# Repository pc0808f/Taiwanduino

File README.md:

# Taiwanduino

Hi, this is the official project site of Taiwanduino
* For our hardware design, please go to [/hardware][hw]
* Our software stuff (bootloader, driver, Arduino sketch...etc) is at [/software][sw]
* Our holder model has been released, it's located at [/holder][hd]

For installation or assembly instructions, see our [Wiki page][wiki]
Like our facebook [fan page][fb] for more info, online shop or donations!

[Changelog]
2025/11/05 (pc0808f fork) - v1.0.3
Fixed: Support for USBasp/USBtiny programmer with custom USB ID 1209:5457
Changed: Reverted to v1.0.2 style using arduino:usbtiny as upload tool
Programmer: "Taiwanduino" option available (uses local avrdude.conf for custom USB IDs)
Note: Direct upload uses Arduino core tools; "Upload Using Programmer" supports VID:1209 PID:5457

2025/10/29 (pc0808f fork) - v1.0.2
Fixed: Examples now visible in Arduino IDE after Board Manager installation
Added library.properties file for bundled library
Updated board package structure to follow Arduino specification

2025/10/28 (pc0808f fork) - v1.0.1
Updated board manager URL to pc0808f fork version
Re-committed zip file for GitHub Pages sync

2017/9/24
Add a 7 tones simple instrument example sketch

2016/11/11
Support for the latest CapacitiveSensor library from the Library Manager

2016/10/31
Holder v1.0 released

2016/10/27
Add pcm audio converter tools/pcm_converter
Cleanup example sketches

***

*Read this in other languages: [English](README.md), [繁體中文](README.zh-TW.md).*

   [wiki]: <https://github.com/pc0808f/Taiwanduino/wiki>
   [hw]: <https://github.com/pc0808f/Taiwanduino/tree/master/hardware>
   [sw]: <https://github.com/pc0808f/Taiwanduino/tree/master/software>
   [hd]: <https://github.com/pc0808f/Taiwanduino/tree/master/holder>
   [fb]: <https://www.facebook.com/Taiwanduino>

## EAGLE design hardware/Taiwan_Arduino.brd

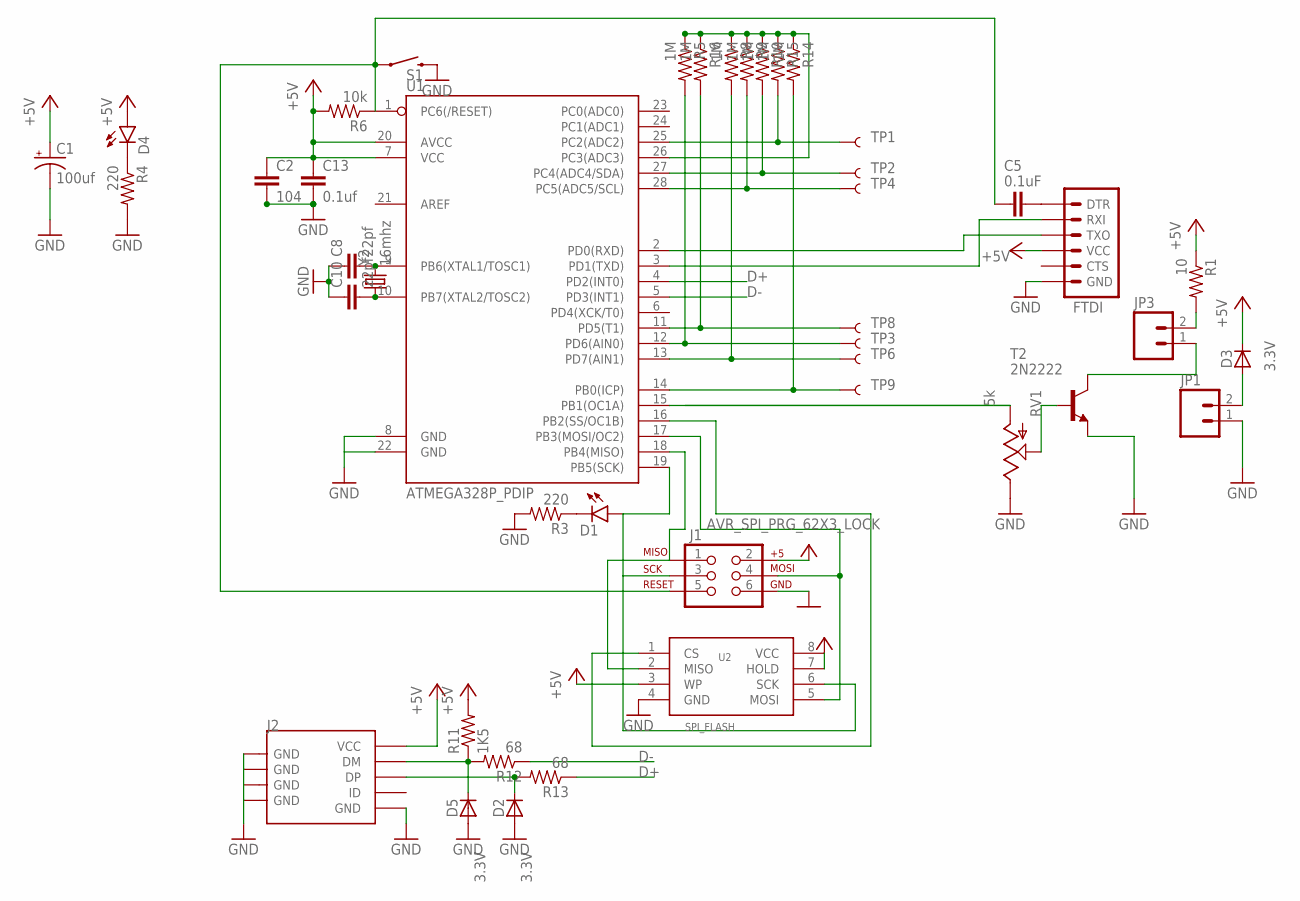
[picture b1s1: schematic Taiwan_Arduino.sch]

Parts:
C1: 100uf; E2,5-5
C2: 104; CAP-PTH-5MM
C5: 0.1uF; CAP-PTH-5MM
C8, C10: 22pf; CAP-PTH-5MM
C13: 0.1uf; CAP-PTH-5MM
D1, D4: LED3MM
D2, D3, D5: 3.3V; 0204V
FTDI: ARDUINO_SERIAL_PROGRAMLOCK; 1X06_LOCK
J1: AVR_SPI_PRG_62X3_LOCK; 2X3_LOCK
J2: USB-MINIUSB-5P-TH; MINI-5P
JP1: Battery; 1X02
JP3: M021X02_NO_SILK; 1X02_NO_SILK
R1: 10; AXIAL-0.1
R3, R4: 220; AXIAL-0.1
R5, R8, R9, R10, R15, R16: 1M; AXIAL-0.1
R6: 10k; AXIAL-0.1
R11: 1K5; AXIAL-0.1
R12, R13: 68; AXIAL-0.1
R14: 1M; AXIAL-0.4
RV1: 5k; ALPS_POT
S1: SWITCH-MOMENTARY-2PTH; TACTILE-PTH
T2: 2N2222; TO92-EBC-OVAL
TP1, TP2, TP3, TP4, TP6, TP8, TP9: TEST-POINT; PADBIG
U1: ATMEGA328P_PDIP; DIL28-3
U2: SPI_FLASH; DIL08
Y2: 16mhz; HC49U-V

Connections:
1: R8.P$2 (2), TP6.P$1, U1.13 (PD7(AIN1))
+5V: C1.+, C2.1, C13.1, D3.2 (C), D4.A, FTDI.4 (VCC), J1.2, J2.VCC, R1.P$1 (1), R6.P$2 (2), R11.P$2 (2), U1.7 (VCC), U1.20 (AVCC), U2.3 (WP), U2.7 (HOLD), U2.8 (VCC)
D+: R13.P$1 (1), U1.4 (PD2(INT0))
D-: R12.P$1 (1), U1.5 (PD3(INT1))
GND: C1.-, C2.2, C8.1, C10.1, C13.2, D2.1 (A), D5.1 (A), FTDI.6 (GND), J1.6, J2.GND, J2.S1 (GND), J2.S2 (GND), J2.S3 (GND), J2.S4 (GND), JP1.1, R3.P$2 (2), R4.P$2 (2), RV1.P$1 (E), S1.3 (2), T2.E, U1.8 (GND), U1.22 (GND), U2.4 (GND)
unnamed: JP3.2, R1.P$2 (2)
unnamed: RV1.P$3 (A), U1.15 (PB1(OC1A))
unnamed: R14.P$2 (2), TP9.P$1, U1.14 (PB0(ICP))
unnamed: C8.2, U1.9 (PB6(XTAL1/TOSC1)), Y2.2
unnamed: R15.P$2 (2), TP1.P$1, U1.25 (PC2(ADC2))
unnamed: D1.A, J1.3, U1.19 (PB5(SCK)), U2.6 (SCK)
unnamed: R10.P$2 (2), TP2.P$1, U1.27 (PC4(ADC4/SDA))
unnamed: R9.P$2 (2), TP4.P$1, U1.28 (PC5(ADC5/SCL))
unnamed: FTDI.3 (TXO), U1.2 (PD0(RXD))
unnamed: J1.1, U1.18 (PB4(MISO)), U2.2 (MISO)
unnamed: R5.P$1 (1), R8.P$1 (1), R9.P$1 (1), R10.P$1 (1), R14.P$1 (1), R15.P$1 (1), R16.P$1 (1), U1.26 (PC3(ADC3))
unnamed: JP3.1, T2.C
unnamed: C10.2, U1.10 (PB7(XTAL2/TOSC2)), Y2.1
unnamed: FTDI.2 (RXI), U1.3 (PD1(TXD))
unnamed: D5.2 (C), J2.DM, R11.P$1 (1), R12.P$2 (2)
unnamed: D2.2 (C), J2.DP, R13.P$2 (2)
unnamed: R16.P$2 (2), TP8.P$1, U1.11 (PD5(T1))
unnamed: D3.1 (A), JP1.2
unnamed: D1.K (C), R3.P$1 (1)
unnamed: RV1.P$2 (S), T2.B
unnamed: J1.4, U1.17 (PB3(MOSI/OC2)), U2.5 (MOSI)
unnamed: D4.K (C), R4.P$1 (1)
unnamed: C5.2, FTDI.1 (DTR)
unnamed: U1.16 (PB2(SS/OC1B)), U2.1 (CS)
unnamed: R5.P$2 (2), TP3.P$1, U1.12 (PD6(AIN0))
RST: C5.1, J1.5, R6.P$1 (1), S1.1, U1.1 (PC6(/RESET))

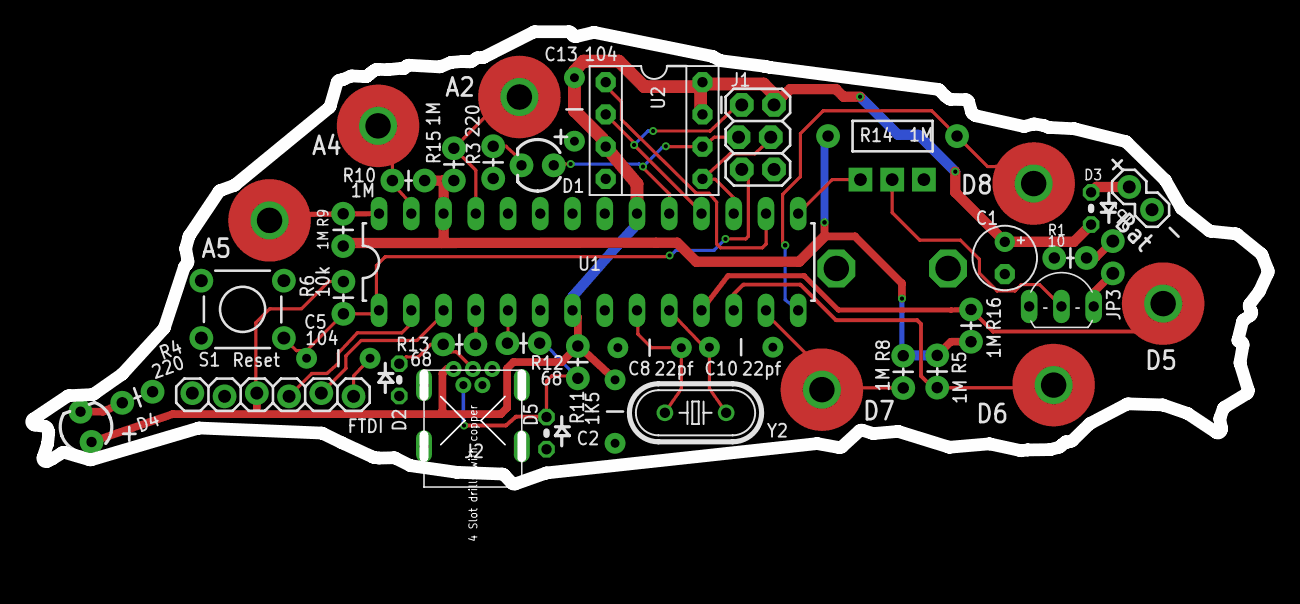
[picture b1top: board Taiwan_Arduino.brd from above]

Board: 2 copper layers, 97.4 x 35.6 mm, 43 parts (0 on the bottom side), 31 nets.

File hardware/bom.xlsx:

Qty | Value | Device | Package | Parts | Description
1 |  | ARDUINO_SERIAL_PROGRAMLOCK | 1X06_LOCK | FTDI | FTDI connector footprints
2 |  | LED3MM | LED3MM | D1, D4 | LEDs
1 | 10 | RESISTOR | 1/4W | R1 | Resistor
1 |  | USB-MINIUSB-5P-TH | MINI-5P | J2
1 | 0.1uF | CAP | CAP-PTH-SMALL | C5 | Capacitor
2 | 0.1uf | CAP | CAP-PTH-SMALL | C2, C13 | Capacitor
1 | 100uf | CPOL-USE2.5-5 | E2,5-5 | C1 | POLARIZED CAPACITOR, American symbol
1 | 10k | RESISTOR | 1/4W | R6 | Resistor
1 | 16mhz | CRYSTAL | HC49U-V | Y2 | Various standard crystals. Proven footprints.
1 | 1K5 | RESISTOR | 1/4W | R11 | Resistor
7 | 1M | RESISTOR | 1/4W | R5, R8, R10, R15, R16,R9, R14 | Resistor
2 | 220 | 1/4W | 1/4W | R3, R4 | Resistor
2 | 22pf | CAP | CAP-PTH-SMALL | C8, C10 | Capacitor
1 | 2N | 2N2222 | TO92-EBC-OVAL | T2 | NPN TRANSISTOR
2 | 3.3V | DIODE-VERTDIODE_SM_VERT | 0204V | D2, D5 | DIODE
1 | 5k | POT | ALPS_POT | RV1
2 | 68 | RESISTOR | 1/4W | R12, R13 | Resistor
1 | ATMEGA328P | ATMEGA328P | DIL28-3 | U1 | uC used in the Arduino
1 | M02X03 | AVR_ISP | 2X3_LOCK | J1 | AVR ISP 6 Pin
1 | M02 | M02JST-PTH-VERT | JST-2-PTH-VERT | JP3 | Standard 2-pin 0.1 header. Use with"
1 | SPI_FLASH-X25XX | SPI_FLASH-X25XX | DIL08 | U$1 | 8pin SPI Flash series x25xx. Works with devices like W25X32 and BR25L32
1 | SWITCH-MOMENTARY-2PTH | SWITCH-MOMENTARY-2PTH | TACTILE-PTH | S1 | Various NO switches- pushbuttons, reed, etc

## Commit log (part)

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2016-03-18 Replaace bypass cap
2016-03-19 Layout fixed
    1.reduce via under the 328p mcu
    2.fix the reset pin routing of the isp header
    3.beef up the power/ground wires near C13 / reset button and USB shell
    4.rotate the speaker header and transistors 45 deg
    5.make more space for capacitor C1/C2
2016-03-19 Added files via upload
    1.change usb D+D- lines to top layer
    2.reroute the VCC line between C13 and EEPROM to prevent TP1 isolated from ground plane
    3.fix the SCK line from ISP header to EEPROM
2016-03-21 Improve touch pad grounding
2016-03-21 improve Cap sense
2016-03-26 Ver 1.0
2016-03-29 Ver 0.9
2016-04-11 28mm/26mm round speaker compatible
    logo text not joined in stl
    0.5mm speaker protection film
2016-04-24 add Driver and Arduino Plugin
2016-04-25 add tag on IO
2016-04-25 add tag on FTDI port
2016-04-25 add FTDI pin labels
2016-04-25 add FTDI Tag
2016-04-26 Fix 10 ohm R1
2016-05-08 add tool
2016-05-08 change readme
2016-05-12 README
2016-05-14 added example and its lib
2016-05-18 Add topcopper PDF file
2016-05-18 add top copper
2016-05-19 Added program to upload wav
2016-05-26 Added screw holes and battery holder
2016-06-03 Fix Arduino plugin
2016-06-06 Change board name and avrdude.conf position
2016-08-08 Add Sch in pdf
2016-08-12 add boardmanager support
2016-09-19 add facebook fanpage
2016-10-23 fixed multiple issue
    1. sketch function compilling problem
    2. rename case to holder, prepare for release
    3. cleanup EEPROM_Playback sketch
2016-10-27 new tool release
    1. new pcm converter release
    2. cleanup all the example sketch
    3. add readme of /software
2016-10-27 new tool release
    delete missupload files
2016-10-30 holder v1.0 released
2016-10-31 holder released v1.0
2016-10-31 fixed win32 compatibility
2016-11-01 english translation
2016-11-01 seperate translated readmes
2016-11-01 fix links
2016-11-11 fix win32 compatibility
    add download for libgcc_s_sjl-1.dll
    change Libav32 to libav-i686-w64-mingw32-11.7
2016-11-11 add gitignore
2016-11-11 fix library issue
    switch to original CapacitiveSensor library instead of the costomized
    one
2016-11-11 remove customized library
    1. remove customized CapacitiveSensor library
    2. update READMEs
2017-03-28 Fix hyperlinks
2017-06-06 fix inconsistent file types
    fix inconsistent file types unsigned char into uni8_t to match the test
    samples in comment
2017-08-09 fix line ending configuration
2017-08-10 Fix readme language swapped problem
2017-09-24 A 7 tones simple instrument
    A 7 tones simple instrument
2017-09-24 update for 7keys
2025-10-28 Final naming convention for pc0808f's Taiwanduino fork
2025-10-28 Re-commit zip file for Pages sync
2025-10-28 Rename taiwanduino-1.0.1.zip to Taiwanduino-1.0.1.zip
2025-10-29 Update changelog for v1.0.2 release
2025-11-05 update to 1.0.4 with driver

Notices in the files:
parts and their libraries:
SparkFun-Capacitors: Licensing: CC v3.0 Share-Alike You are welcome to use this library for commercial purposes.
SparkFun-DigitalIC: Licensing: Creative Commons ShareAlike 4.0 International - https://creativecommons.org/licenses/by-sa/4.0
